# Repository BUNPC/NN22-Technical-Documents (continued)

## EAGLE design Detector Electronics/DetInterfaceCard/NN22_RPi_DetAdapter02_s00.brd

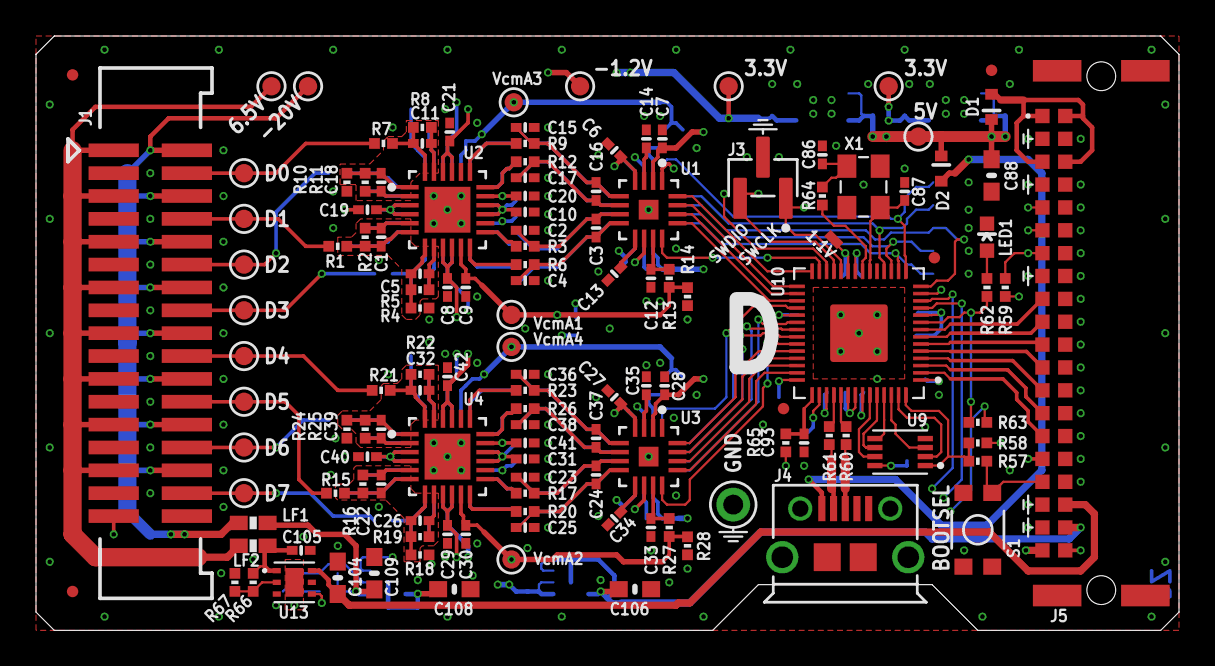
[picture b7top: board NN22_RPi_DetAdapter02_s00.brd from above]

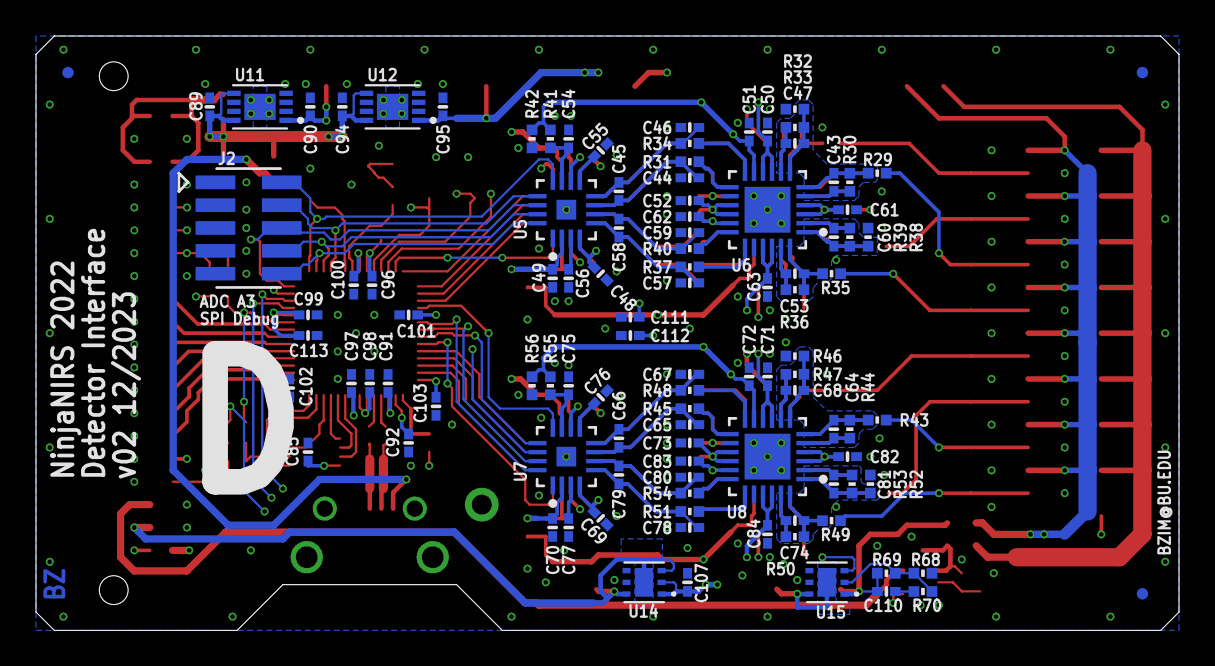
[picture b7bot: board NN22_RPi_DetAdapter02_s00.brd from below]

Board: 6 copper layers, 63.5 x 33.0 mm, 238 parts (105 on the bottom side), 156 nets.

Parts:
C1, C5, C11, C18, C22, C26, C32, C39, C43, C47, C53, C60, C64, C68, C74, C81: 330p; 0402-CAP
C2, C3, C4, C15, C16, C17, C23, C24, C25, C36, C37, C38, C44, C45, C46, C57, C58, C59, C65, C66, C67, C78, C79, C80: 1n; 0402-CAP
C6, C7, C12, C14, C27, C28, C33, C35, C48, C49, C54, C56, C69, C70, C75, C77: 1u; 0402-CAP
C8, C9, C10, C13, C19, C20, C21, C29, C30, C31, C34, C40, C41, C42, C50, C51, C52, C55, C61, C62, C63, C71, C72, C73, C76, C82, C83, C84, C85, C96, C97, C98, C99, C100, C101, C102, C103: 0.1u; 0402-CAP
C86, C87: 27p; 0402-CAP
C88, C104, C106, C108, C109: 10u; 0603-CAP
C89, C90, C91, C92, C93, C94, C95, C105, C107, C111, C112, C113: 4.7u; 0402-CAP
C110: 33n; 0402-CAP
D1, D2: SBR1A20T5; SOD523
FID1, FID2, FID3, FID4, FID5, FID6, FID7, FID8: FIDUCIALUFIDUCIAL; MICRO-FIDUCIAL
J1: M17X2; M17X2_0.050_SHF
J2: M05X2_SMD_0.050_NOCREAM; M05X2_0.050_SMD_NO_CREAM
J3: M03X1_0.050_SMD_NO_CREAM
J4: USB-MICRO
J5: M20X2_HARFLEX_M
LED1: LED-0603
LF1, LF2: FERRITE0603; 0603-FER
R1, R4, R7, R10, R13, R14, R15, R18, R21, R24, R27, R28, R29, R32, R35, R38, R41, R42, R43, R46, R49, R52, R55, R56: 18k; 0402-RES
R2, R5, R8, R11, R16, R19, R22, R25, R30, R33, R36, R39, R44, R47, R50, R53: 2.2k; 0402-RES
R3, R6, R9, R12, R17, R20, R23, R26, R31, R34, R37, R40, R45, R48, R51, R54, R65: 33; 0402-RES
R57, R62, R64: 1.2k; 0402-RES
R58, R59, R67: 100k; 0402-RES
R60, R61: 27; 0402-RES
R63: DNP; 0402-RES
R66: 30k; 0402-RES
R68, R70: 10k; 0402-RES
R69: 154k; 0402-RES
S1: SWITCH-MOMENTARY-2SMD-3; TACTILE_SWITCH_SMD-3
TP1, TP2, TP3, TP4, TP5, TP6, TP7, TP8, TP9, TP11, TP12, TP13, TP15, TP16, TP17, TP18, TP19, TP22: TESTPOINT_ROUND; TESTPAD_ROUND
TP20: TESTPOINT1X01; 1X01
TP21: TESTPOINTPADSMALL; TESTPAD_SMALL
U1, U3, U5, U7: AD7380; LFCSP16
U2, U4, U6, U8: ADA4940-2; LFCSP24
U9: W25Q_USON; USON8L-2X3MM
U10: RP2040; QFN-56_EP
U11, U12: MCP1755_DFN; DFN8_2X3MM
U13: ADP7142_WSON; WSON6
U14, U15: ADP7182_WSON; WSON6
X1: CRYSTAL-3.2-2.5

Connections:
/CS_A1: U1.12, U10.27
/CS_A2: U3.12, U10.37
/CS_A3: J2.2, U5.12, U10.15
/CS_A4: U7.12, U10.32
A_COMM: J1.33, R63.2
BOOTSEL: J5.B17, R57.1, S1.4
DET0: J1.4, R7.1, TP4.P$1
DET1: J1.8, R1.1, TP1.P$1
DET2: J1.12, R29.1, TP9.P$1
DET3: J1.16, R35.1, TP11.P$1
DET4: J1.20, R21.1, TP7.P$1
DET5: J1.24, R15.1, TP6.P$1
DET6: J1.28, R43.1, TP13.P$1
DET7: J1.32, R49.1, TP15.P$1
GND: C2.1, C4.2, C6.2, C7.2, C8.2, C9.2, C10.2, C12.2, C13.2, C14.2, C15.1, C17.2, C19.2, C20.2, C21.2, C23.1, C25.2, C27.2, C28.2, C29.2, C30.2, C31.2, C33.2, C34.2, C35.2, C36.1, C38.2, C40.2, C41.2, C42.2, C44.1, C46.2, C48.2, C49.2, C50.2, C51.2, C52.2, C54.2, C55.2, C56.2, C57.1, C59.2, C61.2, C62.2, C63.2, C65.1, C67.2, C69.2, C70.2, C71.2, C72.2, C73.2, C75.2, C76.2, C77.2, C78.1, C80.2, C82.2, C83.2, C84.2, C85.2, C86.2, C87.2, C88.2, C89.2, C90.2, C91.2, C92.2, C93.2, C94.2, C95.2, C96.2, C97.2, C98.2, C99.2, C100.2, C101.2, C102.2, C103.2, C104.2, C105.2, C106.1, C107.1, C108.1, C109.1, C111.2, C112.1, C113.2, J1.3, J1.7, J1.11, J1.15, J1.19, J1.23, J1.27, J1.31, J2.1, J2.3, J2.5, J2.7, J2.9, J3.2, J4.5, J4.SH1, J4.SH2, J4.SH3, J4.SH4, J4.SH5, J4.SH6, J5.A2, J5.A4, J5.A5, J5.A6, J5.A7, J5.A8, J5.A9, J5.A10, J5.A11, J5.A12, J5.A13, J5.A14, J5.A15, J5.A16, J5.A17, J5.A20, J5.B2, J5.B4, J5.B8, J5.B18, J5.B19, LED1.C, R4.1, R10.1, R14.1, R18.1, R24.1, R28.1, R32.1, R38.1, R42.1, R46.1, R52.1, R56.1, R67.1, R68.2, S1.1, TP20.1, U1.1, U1.10, U1.EP, U2.EP, U3.1, U3.10, U3.EP, U4.EP, U5.1, U5.10, U5.EP, U6.EP, U7.1, U7.10, U7.EP, U8.EP, U9.4, U10.19, U10.PAD, U11.4, U11.P, U12.4, U12.P, U13.3, U13.PAD, U14.5, U15.5, X1.2, X1.4
GPIO00: J5.B15, U10.2
GPIO01: J5.B14, U10.3
GPIO02: J5.B13, U10.4
GPIO03: J5.B12, U10.5
GPIO04: J5.B11, U10.6
GPIO05: J5.B10, U10.7
GPIO06: J5.B9, U10.8
LED: R62.2, R63.1, U10.9
unnamed: R3.1, U2.13
unnamed: R6.1, U2.12
unnamed: C2.2, C3.1, R3.2, U1.7
unnamed: C3.2, C4.1, R6.2, U1.8
unnamed: C11.2, R8.2, U2.23
unnamed: C12.1, R13.2, U1.11
unnamed: C13.1, U1.9
unnamed: C14.1, U1.3
unnamed: C18.2, R11.2, U2.2
unnamed: R17.1, U4.13
unnamed: R9.1, U2.19
unnamed: R12.1, U2.18
unnamed: C15.2, C16.1, R9.2, U1.5
unnamed: C16.2, C17.1, R12.2, U1.6
unnamed: R20.1, U4.12
unnamed: C87.1, U10.20, X1.3
unnamed: C86.1, R64.2, X1.1
unnamed: R64.1, U10.21
unnamed: C1.1, R1.2, R2.1, U2.6
unnamed: C1.2, R2.2, U2.5
unnamed: C5.2, R5.2, U2.8
unnamed: C5.1, R4.2, R5.1, U2.7
unnamed: C11.1, R7.2, R8.1, U2.24
unnamed: C18.1, R10.2, R11.1, U2.1
unnamed: C23.2, C24.1, R17.2, U3.7
unnamed: C24.2, C25.1, R20.2, U3.8
unnamed: R68.1, R69.2, R70.2, U15.2
unnamed: R66.1, R67.2, U13.2
unnamed: R60.1, U10.47
unnamed: R61.1, U10.46
unnamed: C33.1, R27.2, U3.11
unnamed: C34.1, U3.9
unnamed: C35.1, U3.3
unnamed: J4.2, R61.2
unnamed: J4.3, R60.2
unnamed: R23.1, U4.19
unnamed: R26.1, U4.18
unnamed: C36.2, C37.1, R23.2, U3.5
unnamed: C37.2, C38.1, R26.2, U3.6
unnamed: C93.1, R65.2, U10.43
unnamed: C22.1, R15.2, R16.1, U4.6
unnamed: C22.2, R16.2, U4.5
unnamed: C26.2, R19.2, U4.8
unnamed: C26.1, R18.2, R19.1, U4.7
unnamed: C32.1, R21.2, R22.1, U4.24
unnamed: C39.1, R24.2, R25.1, U4.1
unnamed: C32.2, R22.2, U4.23
unnamed: C39.2, R25.2, U4.2
unnamed: R31.1, U6.13
unnamed: R34.1, U6.12
unnamed: C44.2, C45.1, R31.2, U5.7
unnamed: C45.2, C46.1, R34.2, U5.8
unnamed: C54.1, R41.2, U5.11
unnamed: C55.1, U5.9
unnamed: C56.1, U5.3
unnamed: R37.1, U6.19
unnamed: R40.1, U6.18
unnamed: C57.2, C58.1, R37.2, U5.5
unnamed: C58.2, C59.1, R40.2, U5.6
unnamed: C43.1, R29.2, R30.1, U6.6
unnamed: C43.2, R30.2, U6.5
unnamed: C47.2, R33.2, U6.8
unnamed: C47.1, R32.2, R33.1, U6.7
unnamed: C53.1, R35.2, R36.1, U6.24
unnamed: C60.1, R38.2, R39.1, U6.1
unnamed: C53.2, R36.2, U6.23
unnamed: C60.2, R39.2, U6.2
unnamed: R45.1, U8.13
unnamed: R48.1, U8.12
unnamed: C65.2, C66.1, R45.2, U7.7
unnamed: C66.2, C67.1, R48.2, U7.8
unnamed: C75.1, R55.2, U7.11
unnamed: C76.1, U7.9
unnamed: C77.1, U7.3
unnamed: R51.1, U8.19
unnamed: R54.1, U8.18
unnamed: C78.2, C79.1, R51.2, U7.5
unnamed: C79.2, C80.1, R54.2, U7.6
unnamed: C64.1, R43.2, R44.1, U8.6
unnamed: C64.2, R44.2, U8.5
unnamed: C68.2, R47.2, U8.8
unnamed: C68.1, R46.2, R47.1, U8.7
unnamed: C74.1, R49.2, R50.1, U8.24
unnamed: C81.1, R52.2, R53.1, U8.1
unnamed: C74.2, R50.2, U8.23
unnamed: C81.2, R53.2, U8.2
unnamed: C110.1, R70.1
unnamed: LED1.A, R62.1
OPT_EN_VN: U10.12, U15.3
OPT_EN_VP: U10.11, U13.4
QSPI_SCLK: U9.6, U10.52
QSPI_SD0: U9.5, U10.53
QSPI_SD1: U9.2, U10.55
QSPI_SD2: U9.3, U10.54
QSPI_SD3: U9.7, U10.51
QSPI_SS_N: R57.2, R58.1, U9.1, U10.56
RUN: J5.B7, R59.1, U10.26
SCLK_A1: U1.16, U10.28
SCLK_A2: U3.16, U10.38
SCLK_A3: J2.10, U5.16, U10.16
SCLK_A4: U7.16, U10.34
SDI_A1: U1.15, U10.29
SDI_A2: U3.15, U10.39
SDI_A3: J2.8, U5.15, U10.17
SDI_A4: U7.15, U10.35
SDOA_A1: U1.13, U10.31
SDOA_A2: U3.13, U10.41
SDOA_A3: J2.4, U5.13, U10.18
SDOA_A4: U7.13, U10.36
SDOB_A1: U1.14, U10.30
SDOB_A2: U3.14, U10.40
SDOB_A3: J2.6, U5.14, U10.14
SDOB_A4: U7.14, U10.13
SWCLK: J3.1, J5.B6, U10.24
SWDIO: J3.3, J5.B5, U10.25
V1P1: C91.1, C96.1, C97.1, TP21.P$1, U10.23, U10.45, U10.50
V3P3: C7.1, C28.1, C49.1, C70.1, C85.1, C90.1, C92.1, C98.1, C99.1, C100.1, C101.1, C102.1, C103.1, C113.1, J5.B16, R58.2, R59.2, R65.1, TP17.P$1, U1.2, U3.2, U5.2, U7.2, U9.8, U10.1, U10.10, U10.22, U10.33, U10.42, U10.44, U10.48, U10.49, U11.1
V3P3A: C6.1, C8.1, C19.1, C27.1, C29.1, C40.1, C48.1, C50.1, C61.1, C69.1, C71.1, C82.1, C95.1, C111.1, TP18.P$1, U1.4, U2.3, U2.4, U2.9, U2.10, U3.4, U4.3, U4.4, U4.9, U4.10, U5.4, U6.3, U6.4, U6.9, U6.10, U7.4, U8.3, U8.4, U8.9, U8.10, U12.1
V5P0: C88.1, C89.1, C94.1, D1.C, D2.C, TP22.P$1, U11.5, U11.8, U12.5, U12.8
V5P0_IN: D1.A, J5.A1, J5.A3, J5.B1, J5.B3
V6P5: C105.1, LF1.2, R66.2, U13.1
V6P5CON: J1.1, J1.5, J1.9, J1.13, J1.17, J1.21, J1.25, J1.29, LF1.1, TP2.P$1
V9P0: C104.1, J5.A18, U13.6
VBUS: D2.A, J4.1
VN1P2: C10.1, C21.1, C31.1, C42.1, C52.1, C63.1, C73.1, C84.1, C107.2, C112.2, TP19.P$1, U2.15, U2.16, U2.21, U2.22, U4.15, U4.16, U4.21, U4.22, U6.15, U6.16, U6.21, U6.22, U8.15, U8.16, U8.21, U8.22, U14.1, U14.2
VN3P0: C106.2, J5.A19, U14.3, U14.6, U14.PAD
VN20P0: C109.2, C110.2, LF2.2, R69.1, U15.1
VN20P0CON: J1.2, J1.6, J1.10, J1.14, J1.18, J1.22, J1.26, J1.30, LF2.1, TP3.P$1
VN22: C108.2, J5.B20, U15.6, U15.PAD
VOCM_A1: C9.1, C20.1, R13.1, R14.2, TP5.P$1, U2.11, U2.17
VOCM_A2: C30.1, C41.1, R27.1, R28.2, TP8.P$1, U4.11, U4.17
VOCM_A3: C51.1, C62.1, R41.1, R42.2, TP12.P$1, U6.11, U6.17
VOCM_A4: C72.1, C83.1, R55.1, R56.2, TP16.P$1, U8.11, U8.17

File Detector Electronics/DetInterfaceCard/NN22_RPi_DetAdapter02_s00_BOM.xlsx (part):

Designator | Value | Footprint | Populate | MPN | Manufacturer
C1 | 330p | 0402-CAP | 1 | GRM1555C1H331JA01D | Murata
C10 | 0.1u | 0402-CAP | 1 | GRM155R71H104KE14D | Murata
C100 | 0.1u | 0402-CAP | 1 | GRM155R71H104KE14D | Murata
C101 | 0.1u | 0402-CAP | 1 | GRM155R71H104KE14D | Murata
C102 | 0.1u | 0402-CAP | 1 | GRM155R71H104KE14D | Murata
C103 | 0.1u | 0402-CAP | 1 | GRM155R71H104KE14D | Murata
C104 | 10u | 0603-CAP | 1 | GRM188R6YA106MA73D | Murata
C105 | 4.7u | 0402-CAP | 1 | CL05A475MP5NRNC | Samsung
C106 | 10u | 0603-CAP | 1 | GRM188R6YA106MA73D | Murata
C107 | 4.7u | 0402-CAP | 1 | CL05A475MP5NRNC | Samsung
C108 | 10u | 0603-CAP | 1 | GRM188R6YA106MA73D | Murata
C109 | 10u | 0603-CAP | 1 | GRM188R6YA106MA73D | Murata
C11 | 330p | 0402-CAP | 1 | GRM1555C1H331JA01D | Murata
C110 | 33n | 0402-CAP | 1 | GCM155R71E333KA55D | Murata
C111 | 4.7u | 0402-CAP | 1 | CL05A475MP5NRNC | Samsung
C112 | 4.7u | 0402-CAP | 1 | CL05A475MP5NRNC | Samsung
C113 | 4.7u | 0402-CAP | 1 | CL05A475MP5NRNC | Samsung
C12 | 1u | 0402-CAP | 1 | CL05A105KP5NNNC | Samsung
C13 | 0.1u | 0402-CAP | 1 | GRM155R71H104KE14D | Murata
C14 | 1u | 0402-CAP | 1 | CL05A105KP5NNNC | Samsung
C15 | 1n | 0402-CAP | 1 | GRM1555C1H102JA01D | Murata
C16 | 1n | 0402-CAP | 1 | GRM1555C1H102JA01D | Murata
C17 | 1n | 0402-CAP | 1 | GRM1555C1H102JA01D | Murata
C18 | 330p | 0402-CAP | 1 | GRM1555C1H331JA01D | Murata
C19 | 0.1u | 0402-CAP | 1 | GRM155R71H104KE14D | Murata
C2 | 1n | 0402-CAP | 1 | GRM1555C1H102JA01D | Murata
C20 | 0.1u | 0402-CAP | 1 | GRM155R71H104KE14D | Murata
C21 | 0.1u | 0402-CAP | 1 | GRM155R71H104KE14D | Murata
C22 | 330p | 0402-CAP | 1 | GRM1555C1H331JA01D | Murata
C23 | 1n | 0402-CAP | 1 | GRM1555C1H102JA01D | Murata
C24 | 1n | 0402-CAP | 1 | GRM1555C1H102JA01D | Murata
C25 | 1n | 0402-CAP | 1 | GRM1555C1H102JA01D | Murata
C26 | 330p | 0402-CAP | 1 | GRM1555C1H331JA01D | Murata
C27 | 1u | 0402-CAP | 1 | CL05A105KP5NNNC | Samsung
C28 | 1u | 0402-CAP | 1 | CL05A105KP5NNNC | Samsung
C29 | 0.1u | 0402-CAP | 1 | GRM155R71H104KE14D | Murata
C3 | 1n | 0402-CAP | 1 | GRM1555C1H102JA01D | Murata
C30 | 0.1u | 0402-CAP | 1 | GRM155R71H104KE14D | Murata
C31 | 0.1u | 0402-CAP | 1 | GRM155R71H104KE14D | Murata
C32 | 330p | 0402-CAP | 1 | GRM1555C1H331JA01D | Murata
C33 | 1u | 0402-CAP | 1 | CL05A105KP5NNNC | Samsung
C34 | 0.1u | 0402-CAP | 1 | GRM155R71H104KE14D | Murata
C35 | 1u | 0402-CAP | 1 | CL05A105KP5NNNC | Samsung
C36 | 1n | 0402-CAP | 1 | GRM1555C1H102JA01D | Murata
C37 | 1n | 0402-CAP | 1 | GRM1555C1H102JA01D | Murata
C38 | 1n | 0402-CAP | 1 | GRM1555C1H102JA01D | Murata
C39 | 330p | 0402-CAP | 1 | GRM1555C1H331JA01D | Murata
C4 | 1n | 0402-CAP | 1 | GRM1555C1H102JA01D | Murata
C40 | 0.1u | 0402-CAP | 1 | GRM155R71H104KE14D | Murata
C41 | 0.1u | 0402-CAP | 1 | GRM155R71H104KE14D | Murata
C42 | 0.1u | 0402-CAP | 1 | GRM155R71H104KE14D | Murata
C43 | 330p | 0402-CAP | 1 | GRM1555C1H331JA01D | Murata
C44 | 1n | 0402-CAP | 1 | GRM1555C1H102JA01D | Murata
C45 | 1n | 0402-CAP | 1 | GRM1555C1H102JA01D | Murata
C46 | 1n | 0402-CAP | 1 | GRM1555C1H102JA01D | Murata
C47 | 330p | 0402-CAP | 1 | GRM1555C1H331JA01D | Murata
C48 | 1u | 0402-CAP | 1 | CL05A105KP5NNNC | Samsung
C49 | 1u | 0402-CAP | 1 | CL05A105KP5NNNC | Samsung
C5 | 330p | 0402-CAP | 1 | GRM1555C1H331JA01D | Murata
C50 | 0.1u | 0402-CAP | 1 | GRM155R71H104KE14D | Murata
C51 | 0.1u | 0402-CAP | 1 | GRM155R71H104KE14D | Murata
C52 | 0.1u | 0402-CAP | 1 | GRM155R71H104KE14D | Murata
C53 | 330p | 0402-CAP | 1 | GRM1555C1H331JA01D | Murata
C54 | 1u | 0402-CAP | 1 | CL05A105KP5NNNC | Samsung
C55 | 0.1u | 0402-CAP | 1 | GRM155R71H104KE14D | Murata
C56 | 1u | 0402-CAP | 1 | CL05A105KP5NNNC | Samsung
C57 | 1n | 0402-CAP | 1 | GRM1555C1H102JA01D | Murata
C58 | 1n | 0402-CAP | 1 | GRM1555C1H102JA01D | Murata
C59 | 1n | 0402-CAP | 1 | GRM1555C1H102JA01D | Murata
C6 | 1u | 0402-CAP | 1 | CL05A105KP5NNNC | Samsung
C60 | 330p | 0402-CAP | 1 | GRM1555C1H331JA01D | Murata
C61 | 0.1u | 0402-CAP | 1 | GRM155R71H104KE14D | Murata
C62 | 0.1u | 0402-CAP | 1 | GRM155R71H104KE14D | Murata
C63 | 0.1u | 0402-CAP | 1 | GRM155R71H104KE14D | Murata
C64 | 330p | 0402-CAP | 1 | GRM1555C1H331JA01D | Murata
C65 | 1n | 0402-CAP | 1 | GRM1555C1H102JA01D | Murata
C66 | 1n | 0402-CAP | 1 | GRM1555C1H102JA01D | Murata
C67 | 1n | 0402-CAP | 1 | GRM1555C1H102JA01D | Murata
C68 | 330p | 0402-CAP | 1 | GRM1555C1H331JA01D | Murata
C69 | 1u | 0402-CAP | 1 | CL05A105KP5NNNC | Samsung
C7 | 1u | 0402-CAP | 1 | CL05A105KP5NNNC | Samsung
C70 | 1u | 0402-CAP | 1 | CL05A105KP5NNNC | Samsung
C71 | 0.1u | 0402-CAP | 1 | GRM155R71H104KE14D | Murata
C72 | 0.1u | 0402-CAP | 1 | GRM155R71H104KE14D | Murata
C73 | 0.1u | 0402-CAP | 1 | GRM155R71H104KE14D | Murata
C74 | 330p | 0402-CAP | 1 | GRM1555C1H331JA01D | Murata
C75 | 1u | 0402-CAP | 1 | CL05A105KP5NNNC | Samsung
C76 | 0.1u | 0402-CAP | 1 | GRM155R71H104KE14D | Murata
C77 | 1u | 0402-CAP | 1 | CL05A105KP5NNNC | Samsung
C78 | 1n | 0402-CAP | 1 | GRM1555C1H102JA01D | Murata
C79 | 1n | 0402-CAP | 1 | GRM1555C1H102JA01D | Murata
C8 | 0.1u | 0402-CAP | 1 | GRM155R71H104KE14D | Murata
C80 | 1n | 0402-CAP | 1 | GRM1555C1H102JA01D | Murata
C81 | 330p | 0402-CAP | 1 | GRM1555C1H331JA01D | Murata
C82 | 0.1u | 0402-CAP | 1 | GRM155R71H104KE14D | Murata
C83 | 0.1u | 0402-CAP | 1 | GRM155R71H104KE14D | Murata
C84 | 0.1u | 0402-CAP | 1 | GRM155R71H104KE14D | Murata
C85 | 0.1u | 0402-CAP | 1 | GRM155R71H104KE14D | Murata
C86 | 27p | 0402-CAP | 1 | GCM1555C1H270JA16D | Murata
C87 | 27p | 0402-CAP | 1 | GCM1555C1H270JA16D | Murata
C88 | 10u | 0603-CAP | 1 | GRM188R6YA106MA73D | Murata
C89 | 4.7u | 0402-CAP | 1 | CL05A475MP5NRNC | Samsung
C9 | 0.1u | 0402-CAP | 1 | GRM155R71H104KE14D | Murata
C90 | 4.7u | 0402-CAP | 1 | CL05A475MP5NRNC | Samsung
C91 | 4.7u | 0402-CAP | 1 | CL05A475MP5NRNC | Samsung
C92 | 4.7u | 0402-CAP | 1 | CL05A475MP5NRNC | Samsung
C93 | 4.7u | 0402-CAP | 1 | CL05A475MP5NRNC | Samsung
C94 | 4.7u | 0402-CAP | 1 | CL05A475MP5NRNC | Samsung
C95 | 4.7u | 0402-CAP | 1 | CL05A475MP5NRNC | Samsung
C96 | 0.1u | 0402-CAP | 1 | GRM155R71H104KE14D | Murata
C97 | 0.1u | 0402-CAP | 1 | GRM155R71H104KE14D | Murata
C98 | 0.1u | 0402-CAP | 1 | GRM155R71H104KE14D | Murata
C99 | 0.1u | 0402-CAP | 1 | GRM155R71H104KE14D | Murata
D1 | SBR1A20T5 | SOD523 | 1 | SBR1A20T5-7 | Diodes Inc.
D2 | SBR1A20T5 | SOD523 | 1 | SBR1A20T5-7 | Diodes Inc.
FID1 | FIDUCIALUFIDUCIAL | MICRO-FIDUCIAL | 0
FID2 | FIDUCIALUFIDUCIAL | MICRO-FIDUCIAL | 0
FID3 | FIDUCIALUFIDUCIAL | MICRO-FIDUCIAL | 0
FID4 | FIDUCIALUFIDUCIAL | MICRO-FIDUCIAL | 0
FID5 | FIDUCIALUFIDUCIAL | MICRO-FIDUCIAL | 0
FID6 | FIDUCIALUFIDUCIAL | MICRO-FIDUCIAL | 0
FID7 | FIDUCIALUFIDUCIAL | MICRO-FIDUCIAL | 0
FID8 | FIDUCIALUFIDUCIAL | MICRO-FIDUCIAL | 0
J1 | M17X2 | M17X2_0.050_SHF | 1 | SHF-117-01-L-D-SM | Samtec
J2 | M05X2_SMD_0.050_NOCREAM | M05X2_0.050_SMD_NO_CREAM | 0
J3 | M03X1_0.050_SMD_NO_CREAM | M03X1_0.050_SMD_NO_CREAM | 0
J4 | USB-MICRO | USB-MICRO | 1 | 10118194-0001LF | Amphenol Communications Solutions
J5 | M20X2_HARFLEX_M | M20X2_HARFLEX_M | 1 | 15150402601000 | HARTING Elektronik
LED1 |  | LED-0603 | 1 | LTST-C191KRKT | Lite-On
LF1 | FERRITE0603 | 0603-FER | 1 | BLM18AG601SN1D | Murata
LF2 | FERRITE0603 | 0603-FER | 1 | BLM18AG601SN1D | Murata
R1 | 18k | 0402-RES | 1 | RR0510P-183-D | Susumu
R10 | 18k | 0402-RES | 1 | RR0510P-183-D | Susumu
R11 | 2.2k | 0402-RES | 1 | RR0510P-222-D | Susumu
R12 | 33 | 0402-RES | 1 | CRCW040233R0FKEDC | Vishay
R13 | 18k | 0402-RES | 1 | RR0510P-183-D | Susumu
R14 | 18k | 0402-RES | 1 | RR0510P-183-D | Susumu
R15 | 18k | 0402-RES | 1 | RR0510P-183-D | Susumu
R16 | 2.2k | 0402-RES | 1 | RR0510P-222-D | Susumu
R17 | 33 | 0402-RES | 1 | CRCW040233R0FKEDC | Vishay
R18 | 18k | 0402-RES | 1 | RR0510P-183-D | Susumu
R19 | 2.2k | 0402-RES | 1 | RR0510P-222-D | Susumu
R2 | 2.2k | 0402-RES | 1 | RR0510P-222-D | Susumu
R20 | 33 | 0402-RES | 1 | CRCW040233R0FKEDC | Vishay
R21 | 18k | 0402-RES | 1 | RR0510P-183-D | Susumu
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
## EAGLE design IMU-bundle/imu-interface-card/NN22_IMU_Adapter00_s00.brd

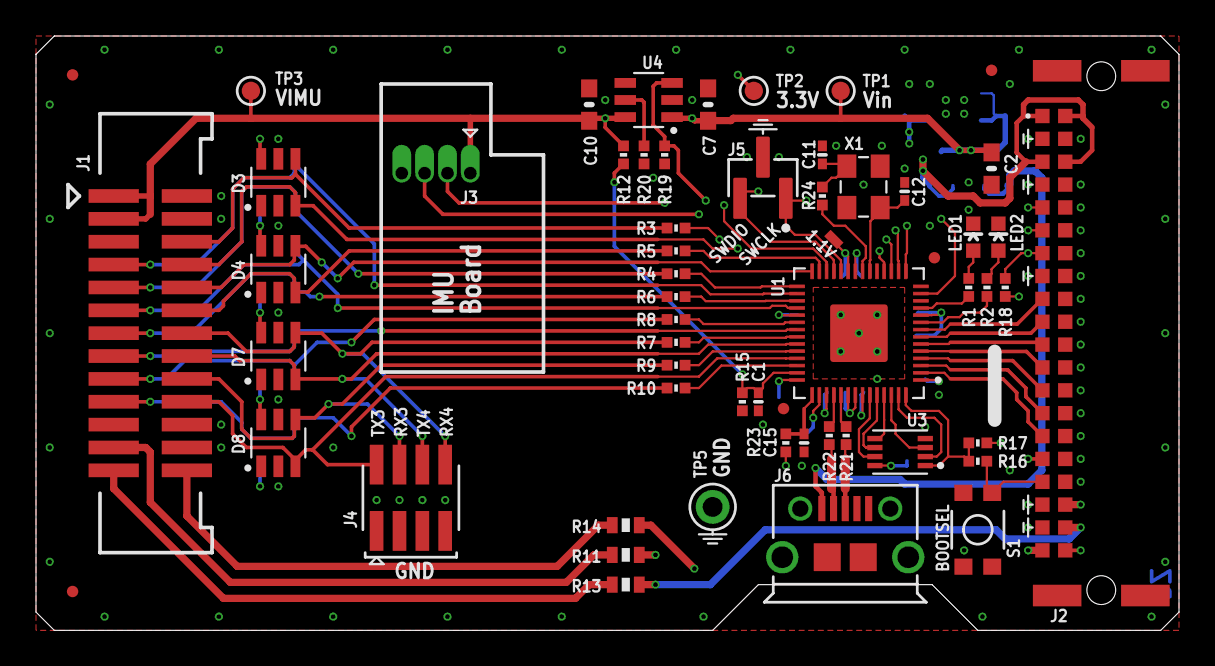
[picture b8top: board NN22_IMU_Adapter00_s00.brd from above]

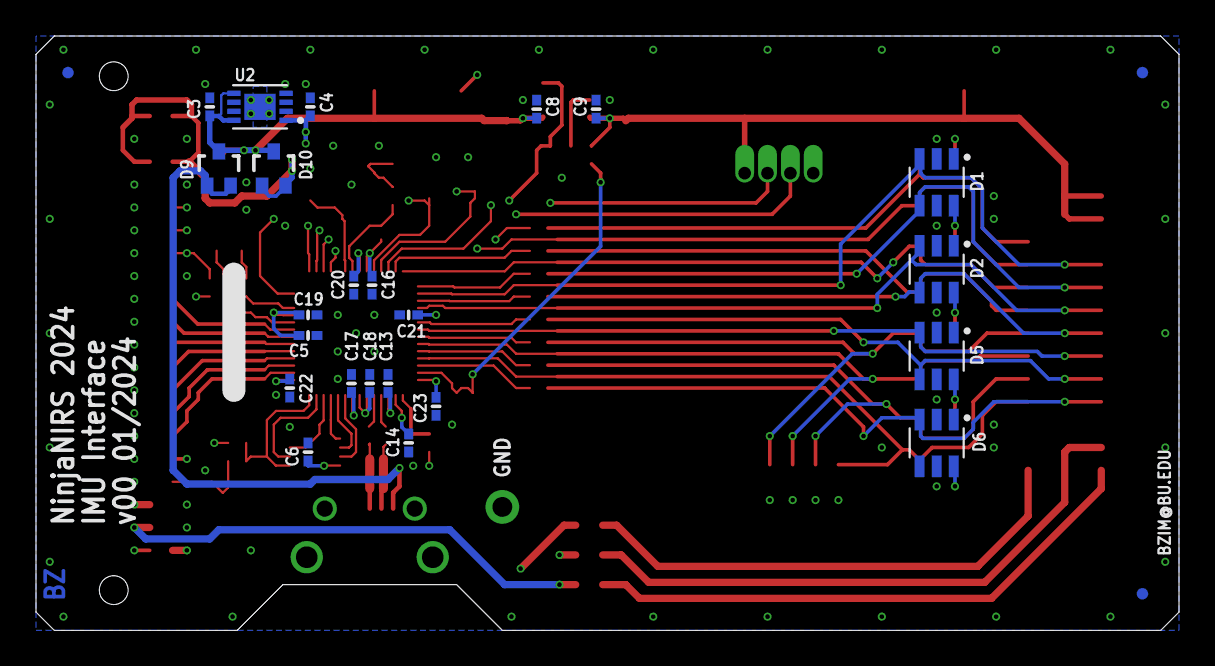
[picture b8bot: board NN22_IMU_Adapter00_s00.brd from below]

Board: 4 copper layers, 63.5 x 33.0 mm, 84 parts (26 on the bottom side), 70 nets.

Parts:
C1, C3, C6, C8, C9, C16, C17, C18, C19, C20, C21, C22, C23: 0.1u; 0402-CAP
C2, C7, C10: 10u; 0603-CAP
C4, C5, C13, C14, C15: 4.7u; 0402-CAP
C11, C12: 27p; 0402-CAP
D1, D2, D3, D4, D5, D6, D7, D8: D1213A-02SO; SOT23-6
D9, D10: BAV70W; SOT323
FID1, FID2, FID3, FID4, FID5, FID6, FID7, FID8: FIDUCIALUFIDUCIAL; MICRO-FIDUCIAL
J1: M13X2_0.050_SHF
J2: M20X2_HARFLEX_M
J3: M04X1_PTH_0.050; M04X1_0.050_PTH
J4: M04X2_0.050_SMD_NO_CREAM
J5: M03X1_0.050_SMD_NO_CREAM
J6: USB-MICRO
LED1, LED2: LED-0603
R1, R2, R10, R16, R24: 1.2k; 0402-RES
R3, R4, R5, R6, R7, R8, R9: 10; 0402-RES
R11, R13, R14: DNP; 0603-RES
R12, R15, R17, R18, R19: 100k; 0402-RES
R20: 82k; 0402-RES
R21, R22: 27; 0402-RES
R23: 33; 0402-RES
S1: SWITCH-MOMENTARY-2SMD-3; TACTILE_SWITCH_SMD-3
TP1, TP2, TP3: TESTPOINT_ROUND; TESTPAD_ROUND
TP4: TESTPOINTPADSMALL; TESTPAD_SMALL
TP5: TESTPOINT1X01; 1X01
U1: RP2040; QFN-56_EP
U2: MCP1755_DFN; DFN8_2X3MM
U3: W25Q_USON; USON8L-2X3MM
U4: AP2265X_SOT; SOT23-6
X1: CRYSTAL-3.2-2.5

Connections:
BOOTSEL: J2.B17, R16.1, S1.4
GND: C1.2, C2.2, C3.2, C4.2, C5.2, C6.2, C7.2, C8.2, C9.2, C10.2, C11.2, C12.2, C13.2, C14.2, C15.2, C16.2, C17.2, C18.2, C19.2, C20.2, C21.2, C22.2, C23.2, D1.2, D2.2, D3.2, D4.2, D5.2, D6.2, D7.2, D8.2, J1.2, J1.4, J1.22, J1.24, J2.A2, J2.A4, J2.A5, J2.A6, J2.A7, J2.A8, J2.A9, J2.A10, J2.A11, J2.A12, J2.A13, J2.A14, J2.A15, J2.A16, J2.A17, J2.A20, J2.B2, J2.B4, J2.B8, J2.B18, J2.B19, J3.4, J4.1, J4.3, J4.5, J4.7, J5.2, J6.5, J6.SH1, J6.SH2, J6.SH3, J6.SH4, J6.SH5, J6.SH6, LED1.C, LED2.C, R15.1, R19.1, R20.1, S1.1, TP5.1, U1.19, U1.PAD, U2.4, U2.P, U3.4, U4.2, X1.2, X1.4
GPIO00: J2.B15, U1.2
GPIO01: J2.B14, U1.3
GPIO02: J2.B13, U1.4
GPIO03: J2.B12, U1.5
GPIO04: J2.B11, U1.6
GPIO05: J2.B10, U1.7
GPIO06: J2.B9, U1.8
IMU_SPARE: D6.3, J1.19, R10.2
IMU_SPARE_PRE: R10.1, U1.40
LED0: R2.2, U1.9
LED1: R1.2, U1.11
unnamed: R20.2, U4.5
unnamed: J1.23, R11.2
unnamed: J1.25, R13.2
unnamed: J1.26, R14.2
unnamed: C12.1, U1.20, X1.3
unnamed: C11.1, R24.2, X1.1
unnamed: R24.1, U1.21
unnamed: R21.1, U1.47
unnamed: R22.1, U1.46
unnamed: J6.2, R22.2
unnamed: J6.3, R21.2
unnamed: C15.1, R23.2, U1.43
unnamed: LED1.A, R1.1
unnamed: LED2.A, R2.1
QSPI_SCLK: U1.52, U3.6
QSPI_SD0: U1.53, U3.5
QSPI_SD1: U1.55, U3.2
QSPI_SD2: U1.54, U3.3
QSPI_SD3: U1.51, U3.7
QSPI_SS_N: R16.2, R17.1, U1.56, U3.1
RUN: J2.B7, R18.1, U1.26
RX0: D1.4, J1.9, R4.2
RX0_PRE: R4.1, U1.29
RX1: D2.4, J1.13, R6.2
RX1_PRE: R6.1, U1.31
RX2: D5.4, J1.17, R8.2
RX2_PRE: R8.1, U1.34
RX3: D8.4, J1.18, J4.4, R9.1
RX3_PRE: R9.2, U1.38
RX4: D7.4, J1.14, J4.8, R7.1
RX4_PRE: R7.2, U1.36
RX5: D3.4, J1.6, R3.1
RX5_PRE: R3.2, U1.17
RX6: D4.3, J1.12, R5.1
RX6_PRE: R5.2, U1.27
RX7: J3.3, U1.15
SWCLK: J2.B6, J5.1, U1.24
SWDIO: J2.B5, J5.3, U1.25
TX0: D1.3, J1.7, U1.30
TX1: D2.3, J1.11, U1.32
TX2: D5.3, J1.15, U1.35
TX3: D8.3, J1.20, J4.2, U1.39
TX4: D7.3, J1.16, J4.6, U1.37
TX5: D3.3, J1.8, U1.18
TX6: D4.4, J1.10, U1.28
TX7: J3.2, U1.16
V1P1: C13.1, C16.1, C17.1, TP4.P$1, U1.23, U1.45, U1.50
V3P3: C4.1, C5.1, C6.1, C14.1, C18.1, C19.1, C20.1, C21.1, C22.1, C23.1, D1.6, D2.6, D3.6, D4.6, D5.6, D6.6, D7.6, D8.6, J2.B16, R17.2, R18.2, R23.1, TP2.P$1, U1.1, U1.10, U1.22, U1.33, U1.42, U1.44, U1.48, U1.49, U2.1, U3.8
V9P0: J2.A18, R11.1
VBUS: D9.1, D9.2, J6.1
VIMU: C9.1, C10.1, J1.1, J1.3, J3.1, R12.2, TP3.P$1, U4.6
VIMU_EN: R19.2, U1.13, U4.3
VIN: C2.1, C3.1, C7.1, C8.1, D9.3, D10.3, TP1.P$1, U2.5, U2.8, U4.1
VIN_BP: D10.1, D10.2, J2.A1, J2.A3, J2.B1, J2.B3
VIN_SENSE: C1.1, R12.1, R15.2, U1.41
VN3P0: J2.A19, R13.1
VN22: J2.B20, R14.1

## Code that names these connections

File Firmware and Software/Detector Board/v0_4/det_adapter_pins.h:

// ---  NinjaNIRS 2022  ---
// Pin constants for NN22_RPi_DetAdapter00_s02_R66R67 board
//
// Initial version: 2022-12-12
// Major revision: 2024-04-14 (2 wire ADC read)
// Bernhard Zimmermann - bzim@bu.edu
// Boston University Neurophotonics Center
//


// Backplane pins: GPIO00 - GPIO06
const uint UART_TX_PIN = 0;
const uint UART_RX_PIN = 1;
const uint BOARD_SELECT_PIN = 2;
//const uint TRG_PIN = 3; // check also adcacq_msin.pio
const uint END_CYC_PIN = 4;
const uint STATUS_SELECT_PIN = 5;
const uint RESERVED_PIN = 6;

// Misc Pins
const uint LED_PIN = 7;
const uint OPT_EN_VP_PIN = 8;
const uint OPT_EN_VN_PIN = 9;

// ADC pins
// 4 ADCs with dual-data SPI interface
const uint CSN_A3_PIN = 12;
const uint SCLK_A3_PIN = 13;
const uint MOSI_A3_PIN = 14;
const uint MISO_A3_PIN = 15;
const uint MISOB_A3_PIN = 11;
 
const uint CSN_A1_PIN = 16;
const uint SCLK_A1_PIN = 17;
const uint MOSI_A1_PIN = 18;
const uint MISO_A1_PIN = 20;
const uint MISOB_A1_PIN = 19;

const uint CSN_A4_PIN = 21;
const uint SCLK_A4_PIN = 22;
const uint MOSI_A4_PIN = 23;
const uint MISO_A4_PIN = 24;
const uint MISOB_A4_PIN = 10;

const uint CSN_A2_PIN = 25;
const uint SCLK_A2_PIN = 26;
const uint MOSI_A2_PIN = 27;
const uint MISO_A2_PIN = 29;
const uint MISOB_A2_PIN = 28;

// Map adc results to detectors
const uint DET_ADC_MAP[] = {1, 0, 4, 5, 3, 2, 6, 7};

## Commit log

2024-02-12 Acrylic Enclosure Technical Documents
    Uploading all technical documents for the acryllic and 3D printed components in enclosure revision AB
2024-03-22 Updated Assembly Instructions 22 March 2024
2024-05-20 Add files via upload
    Adding documentation for the creation of the ninjaHarness.
2024-05-20 Add files via upload
    Updated version of Assembly Instructions with all part files and drawings 20 May, 2024.
2024-05-20 Delete Acryllic Enclosure Assembly.zip
    Removal of incorrect zip file
2024-05-22 Add Battery Box Files
    Zip files containing Solidworks 2023 parts and Eagle PCB files
2024-05-23 Add battery box BOM file
2024-05-23 Add files via upload
    Splitter box electrical circuit diagram files for sources and detectors.
2024-05-23 Add files via upload
    NN22 Control Board V4 files
2024-05-23 Add files via upload
    Detector backplane files
2024-05-23 Add files via upload
    Detector interface board files
2024-05-23 Add files via upload
    7 slot source backplane files
2024-05-23 Add files via upload
    1 slot source backplane files
2024-05-23 Add files via upload
    Source interface card files
2024-05-23 Add files via upload
    6 slot detector backplane files
2024-05-23 Organization of file system.
2024-05-24 File reorganization
2024-05-24 Source PCB File Reorganization
2024-05-28 Add files from EH.
2024-06-06 Add Firmware Folder
2024-06-09 Update README.md to link to Hardware Forum
2024-06-09 added link to nn22 page at openfnirs
2024-06-17 Add files via upload
    PDF of acrylic enclosure assembly documentation.
2024-06-17 Add Schematic PDF for battery circuit
2024-06-27 Add Detector Files
2024-06-27 Revert "Add Detector Files"
    This reverts commit e8c7ac16a3e25841cc6b62164293f4582a5eec2a.
2024-06-27 Detector File Updates
2024-07-24 Adding Control Board v2 with gerbers.
2024-07-24 Adding gerbers to backplanes.
2024-07-24 Adding gerbers to source interface card.
2024-07-24 Updating detector interface card and adding gerbers.
2024-07-25 Adding IMU interface card.
2024-07-25 ninjaPACK BOM Upload
2024-07-29 Add Colocated Source Part Files
2024-07-29 Colocation Organization
2024-07-29 Added gerbers for co-located source optode.
2024-07-29 Adder gerbers for source optode pcb.
2024-08-05 File system reorganization
2024-08-05 Fix Flex Optode Folder
2024-08-06 Add Standard Detector Files
2024-08-29 Remove Old FIles
2025-02-18 Firmware added
